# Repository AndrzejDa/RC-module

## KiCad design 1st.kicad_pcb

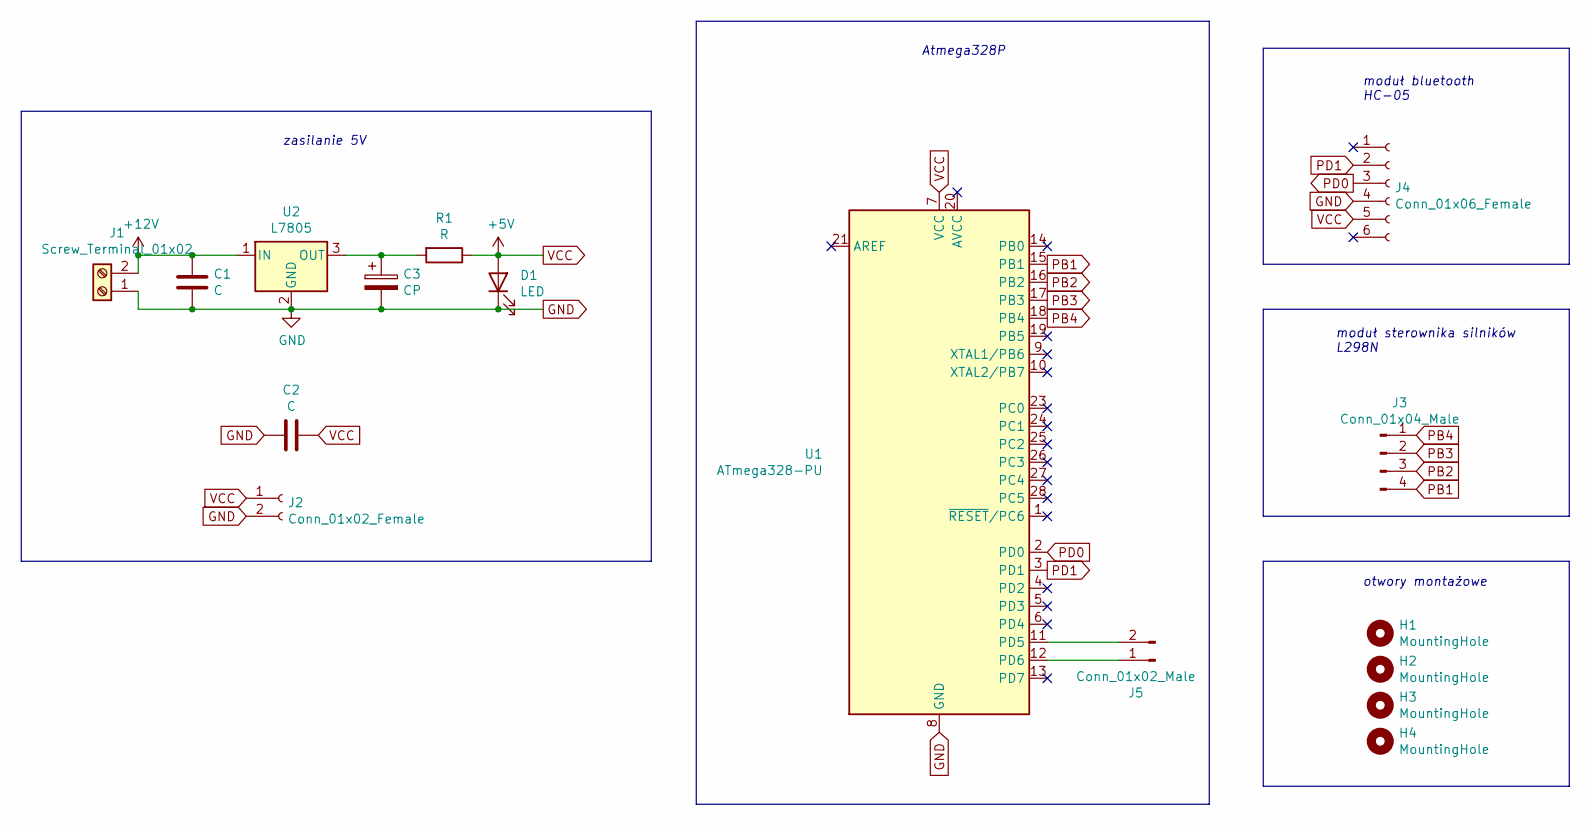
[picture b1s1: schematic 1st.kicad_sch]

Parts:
C1, C2: C; C_Disc_D3.4mm_W2.1mm_P2.50mm
C3: CP; CP_Radial_D4.0mm_P1.50mm
D1: LED; LED_D3.0mm
H1, H2, H3, H4: MountingHole; MountingHole_2.2mm_M2_Pad_Via
J1: Screw_Terminal_01x02; TerminalBlock_Phoenix_MKDS-1,5-2-5.08_1x02_P5.08mm_Horizont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
J2: Conn_01x02_Female; PinSocket_1x02_P2.54mm_Vertical
J3: Conn_01x04_Male; PinHeader_1x04_P2.54mm_Vertical
J4: Conn_01x06_Female; PinSocket_1x06_P2.54mm_Vertical
J5: Conn_01x02_Male; PinHeader_1x02_P2.54mm_Vertical
R1: R; R_Axial_DIN0207_L6.3mm_D2.5mm_P7.62mm_Horizontal
U1: ATmega328-PU; DIP-28_W7.62mm
U2: L7805; TO-220-3_Vertical

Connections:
+12V: C1.1, J1.2, U2.1 (IN)
GND: C1.2, C2.2, C3.2, D1.1 (K), J1.1, J2.2, J4.4, U1.8 (GND), U1.22 (GND), U2.2 (GND)
unnamed: C3.1, R1.2, U2.3 (OUT)
unnamed: J5.1, U1.12 (PD6)
unnamed: J5.2, U1.11 (PD5)
PB1: J3.4, U1.15 (PB1)
PB2: J3.3, U1.16 (PB2)
PB3: J3.2, U1.17 (PB3)
PB4: J3.1, U1.18 (PB4)
PD0: J4.3, U1.2 (PD0)
PD1: J4.2, U1.3 (PD1)
VCC: C2.1, D1.2 (A), J2.1, J4.5, R1.1, U1.7 (VCC)

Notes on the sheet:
moduł sterownika silników L298N
Atmega328P
zasilanie 5V
moduł bluetooth HC-05
otwory montażowe

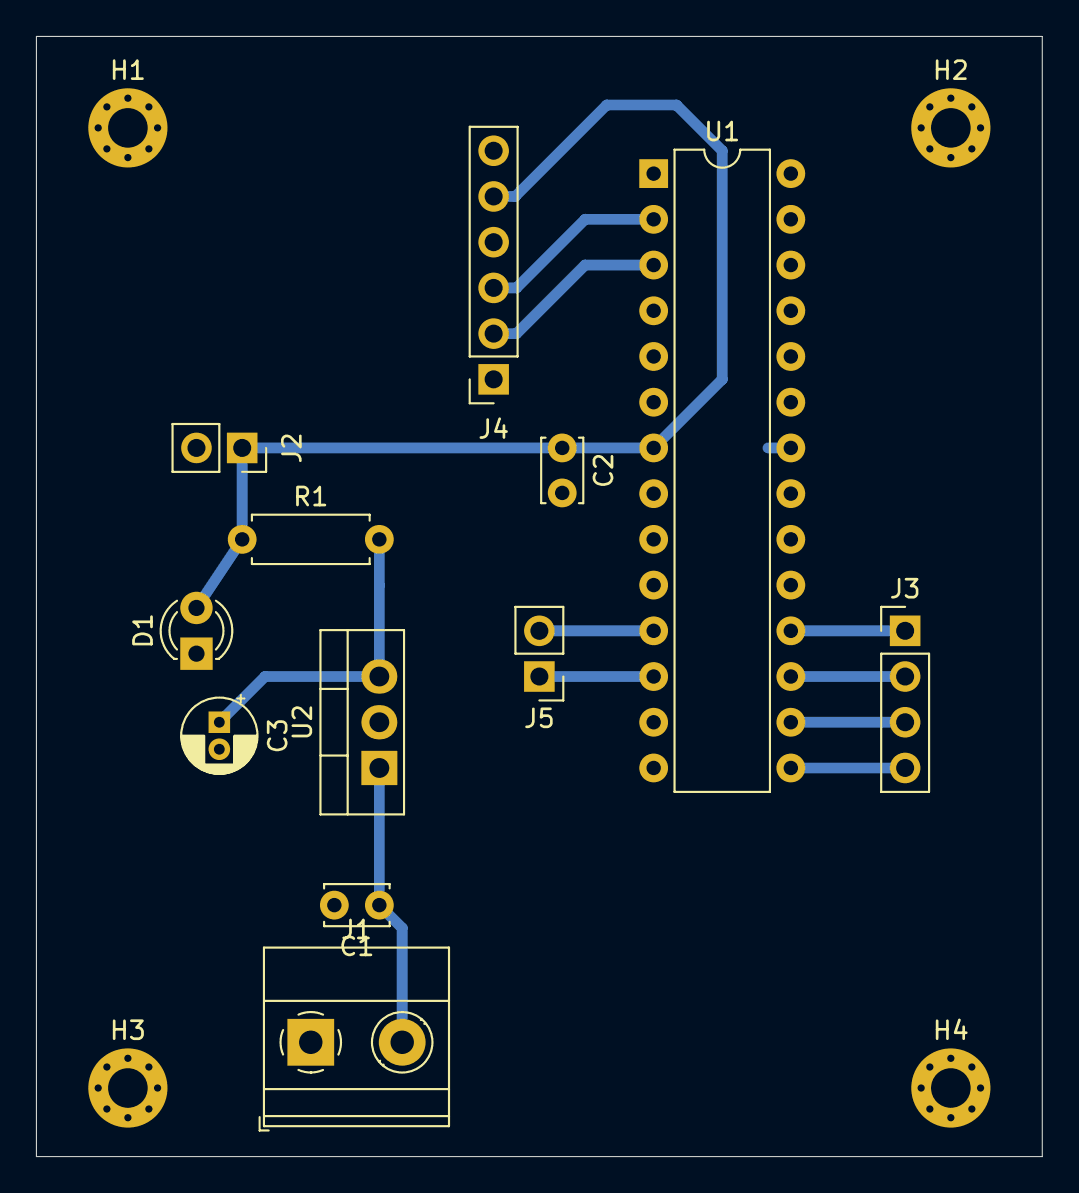
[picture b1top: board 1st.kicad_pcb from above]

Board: 2 copper layers, 55.9 x 62.2 mm, 16 parts (0 on the bottom side), 12 nets.
